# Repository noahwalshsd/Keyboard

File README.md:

# Slim Shady Keyboard
My project is a 65% orthographic mecanical keyboard. It will be more ergonomic than a regular keyboard and mimic a laptop keyboard in its quietness and lack of push depth. 
I needed to get into PCBs. Before this project, I didn't even know what they were or even what PCB meant. I decided to make an ortholinear keyboardbecause I saw them being priced extremely high and I thought I could make it cheaper as my first PCB project. Because it is my first PCB project, I spent well over the suggested time in my learning efforts. I failed many times in nearly everything. I only got the CAD right first try. The cherry on top is that I may qualify for Prototype. 
There is 1 spacebar keycap, 1 3-wide keycap, 5 2-wide keycaps, and 60 small keycaps. 

BOM: You can find it at the BOM.csv tab

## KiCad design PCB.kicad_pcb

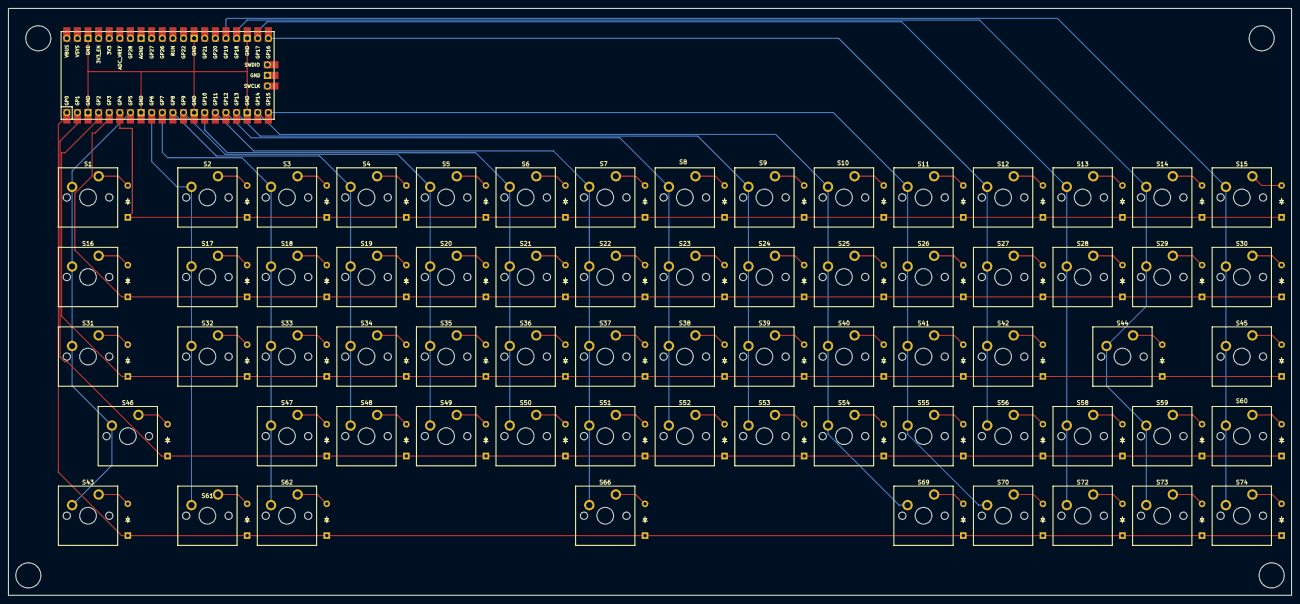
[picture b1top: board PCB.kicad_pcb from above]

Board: 2 copper layers, 307.2 x 140.5 mm, 135 parts (0 on the bottom side), 88 nets.

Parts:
A1: RaspberryPi_Pico; Raspberry_Pi_Pico
D1: hi; Diode_DO-35
D2, D3, D4, D5, D6, D7, D8, D9, D10, D11, D12, D13, D14, D15, D16, D17, D18, D19, D20, D21, D22, D23, D24, D25, D26, D27, D28, D29, D30, D31, D32, D33, D34, D35, D36, D37, D38, D39, D40, D41, D42, D43, D44, D45, D46, D47, D48, D49, D50, D51, D52, D53, D54, D55, D56, D58, D59, D60, D61, D62, D66, D69, D70, D72, D73, D74: Diode_DO-35
S1, S2, S3, S4, S5, S6, S7, S8, S9, S10, S11, S12, S13, S14, S15, S16, S17, S18, S19, S20, S21, S22, S23, S24, S25, S26, S27, S28, S29, S30, S31, S32, S33, S34, S35, S36, S37, S38, S39, S40, S41, S42, S43, S44, S45, S46, S47, S48, S49, S50, S51, S52, S53, S54, S55, S56, S58, S59, S60, S61, S62, S66, S69, S70, S72, S73, S74: MX_PCB_1.00u

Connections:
Co1: A1.7 (GPIO5), S1.1, S16.1, S31.1, S43.1, S46.1
Co2: A1.9 (GPIO6), S2.1, S17.1, S32.1, S61.1
Co3: A1.10 (GPIO7), S3.1, S18.1, S33.1, S47.1, S62.1
Co4: A1.11 (GPIO8), S4.1, S19.1, S34.1, S48.1
Co5: A1.12 (GPIO9), S5.1, S20.1, S35.1, S49.1
Co6: A1.14 (GPIO10), S6.1, S21.1, S36.1, S50.1
Co7: A1.15 (GPIO11), S7.1, S22.1, S37.1, S51.1, S66.1
Co8: A1.16 (GPIO12), S8.1, S23.1, S38.1, S52.1
Co9: A1.17 (GPIO13), S9.1, S24.1, S39.1, S53.1
Co10: A1.19 (GPIO14), S10.1, S25.1, S40.1, S54.1, S69.1
Co11: A1.20 (GPIO15), S11.1, S26.1, S41.1, S55.1, S70.1
Co12: A1.21 (GPIO16), S12.1, S27.1, S42.1, S56.1
Co13: A1.22 (GPIO17), S13.1, S28.1, S58.1, S72.1
Co14: A1.24 (GPIO18), S14.1, S29.1, S44.1, S59.1, S73.1
Co15: A1.25 (GPIO19), S15.1, S30.1, S45.1, S60.1, S74.1
GND: A1.3 (GND), A1.8 (GND), A1.13 (GND), A1.18 (GND), A1.23 (GND), A1.28 (GND), A1.38 (GND)
unnamed: D1.2 (A), S1.2
unnamed: D2.2 (A), S2.2
unnamed: D3.2 (A), S3.2
unnamed: D4.2 (A), S4.2
unnamed: D5.2 (A), S5.2
unnamed: D6.2 (A), S6.2
unnamed: D7.2 (A), S7.2
unnamed: D8.2 (A), S8.2
unnamed: D9.2 (A), S9.2
unnamed: D10.2 (A), S10.2
unnamed: D11.2 (A), S11.2
unnamed: D12.2 (A), S12.2
unnamed: D13.2 (A), S13.2
unnamed: D14.2 (A), S14.2
unnamed: D15.2 (A), S15.2
unnamed: D16.2 (A), S16.2
unnamed: D17.2 (A), S17.2
unnamed: D18.2 (A), S18.2
unnamed: D19.2 (A), S19.2
unnamed: D20.2 (A), S20.2
unnamed: D21.2 (A), S21.2
unnamed: D22.2 (A), S22.2
unnamed: D23.2 (A), S23.2
unnamed: D24.2 (A), S24.2
unnamed: D25.2 (A), S25.2
unnamed: D26.2 (A), S26.2
unnamed: D27.2 (A), S27.2
unnamed: D28.2 (A), S28.2
unnamed: D29.2 (A), S29.2
unnamed: D30.2 (A), S30.2
unnamed: D31.2 (A), S31.2
unnamed: D32.2 (A), S32.2
unnamed: D33.2 (A), S33.2
unnamed: D34.2 (A), S34.2
unnamed: D35.2 (A), S35.2
unnamed: D36.2 (A), S36.2
unnamed: D37.2 (A), S37.2
unnamed: D38.2 (A), S38.2
unnamed: D39.2 (A), S39.2
unnamed: D40.2 (A), S40.2
unnamed: D41.2 (A), S41.2
unnamed: D42.2 (A), S42.2
unnamed: D43.2 (A), S43.2
unnamed: D44.2 (A), S44.2
unnamed: D45.2 (A), S45.2
unnamed: D46.2 (A), S46.2
unnamed: D47.2 (A), S47.2
unnamed: D48.2 (A), S48.2
unnamed: D49.2 (A), S49.2
unnamed: D50.2 (A), S50.2
unnamed: D51.2 (A), S51.2
unnamed: D52.2 (A), S52.2
unnamed: D53.2 (A), S53.2
unnamed: D54.2 (A), S54.2
unnamed: D55.2 (A), S55.2
unnamed: D56.2 (A), S56.2
unnamed: D58.2 (A), S58.2
unnamed: D59.2 (A), S59.2
unnamed: D60.2 (A), S60.2
unnamed: D61.2 (A), S61.2
unnamed: D62.2 (A), S62.2
unnamed: D66.2 (A), S66.2
unnamed: D69.2 (A), S69.2
unnamed: D70.2 (A), S70.2
unnamed: D72.2 (A), S72.2
unnamed: D73.2 (A), S73.2
unnamed: D74.2 (A), S74.2
Ro1: A1.6 (GPIO4), D1.1 (K), D2.1 (K), D3.1 (K), D4.1 (K), D5.1 (K), D6.1 (K), D7.1 (K), D8.1 (K), D9.1 (K), D10.1 (K), D11.1 (K), D12.1 (K), D13.1 (K), D14.1 (K), D15.1 (K)
Ro2: A1.5 (GPIO3), D16.1 (K), D17.1 (K), D18.1 (K), D19.1 (K), D20.1 (K), D21.1 (K), D22.1 (K), D23.1 (K), D24.1 (K), D25.1 (K), D26.1 (K), D27.1 (K), D28.1 (K), D29.1 (K), D30.1 (K)
Ro3: A1.4 (GPIO2), D31.1 (K), D32.1 (K), D33.1 (K), D34.1 (K), D35.1 (K), D36.1 (K), D37.1 (K), D38.1 (K), D39.1 (K), D40.1 (K), D41.1 (K), D42.1 (K), D44.1 (K), D45.1 (K)
Ro4: A1.2 (GPIO1), D46.1 (K), D47.1 (K), D48.1 (K), D49.1 (K), D50.1 (K), D51.1 (K), D52.1 (K), D53.1 (K), D54.1 (K), D55.1 (K), D56.1 (K), D58.1 (K), D59.1 (K), D60.1 (K)
Ro5: A1.1 (GPIO0), D43.1 (K), D61.1 (K), D62.1 (K), D66.1 (K), D69.1 (K), D70.1 (K), D72.1 (K), D73.1 (K), D74.1 (K)

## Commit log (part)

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2025-12-01 new file: .vscode/settings.json new file: kyk.py
2025-12-01 Enhance README with project details and thanks
    Added a personal note about the project and gratitude.
2025-12-01 Journal
    Journal with descending pictures as progress stamps
2025-12-01 Schematic
2025-12-01 CAD.step
2025-12-01 Schematic.kicad_sch
2025-12-01 PCB.zip
2025-12-01 Everything
    Expanded project description and added BOM details with costs and links.
2025-12-01 Firmware
2025-12-01 Update and rename Firmware to l
2025-12-01 Create lol
2025-12-01 done, hopefully
2025-12-02 Update images and BOM details in README
    Replaced two images and added a new BOM entry with costs and links.
2025-12-02 Update Journal with new entries and images
    Added time entry and images for 12/1/25.
2025-12-02 Revise BOM section in README.md
    Updated the Bill of Materials (BOM) section with new items and corrected formatting.
2025-12-02 Rename
2025-12-02 Replace an image in Journal.md
2025-12-02 Fix BOM.csv formatting and header alignment
2025-12-02 Update BOM.csv with new format and data
2025-12-02 Remove items from BOM in README
    Removed several items from the BOM section in the README.
2025-12-02 Update README with BOM location information
    Added a note about the BOM location in the README.
2026-06-29 Add images to Creation_photos.md
2026-06-29 Add Part 1 link to Lapse_links.md
2026-06-29 Add Part 2 link to Lapse_links.md
2026-06-30 Fix formatting of video link in Lapse_links.md
